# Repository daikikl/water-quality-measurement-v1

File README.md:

# Water-Quality Sensor Test PCB — Research Prototype (2024)

## Purpose

This PCB was designed as a hardware test platform for integrating and evaluating low-cost water-quality sensors within a 2024 university research project.

The broader research proposed a low-cost data-capture strategy for monitoring a tributary of the Paraná River in Encarnación, Paraguay.

## Validation status

The PCB was designed and used as part of the sensor-testing stage of the research project.

Specific test results, sensor calibration procedures, measurement datasets, firmware, and broader system-validation details are described only to the extent authorized by the project team and the related publication.

## My contribution

I designed the PCB used as a test platform for the water-quality sensors in this research project.

The board integrates:

- A LilyGO TTGO T3 LoRa32 development board interface.
- RS-485 communication support through a MAX485 transceiver.
- Terminal connections for multiple water-quality sensors.
- Power connections and auxiliary interfaces for prototype testing.

My contribution was focused on PCB design and hardware integration for sensor testing. I did not claim authorship of the complete monitoring strategy, firmware, data analysis, or all experimental validation activities.

## Related publication

Liebel, D., Lugo, D., & Kawamura, D. (2024). *Estrategia de captura de datos con sensores de bajo costo para la gestión de calidad de agua del afluente del Río Paraná*. Revista Impacto, 4(1), 1–12.

[Read the publication](https://revistas.uni.edu.py/index.php/impacto/article/view/504)

## PCB layout

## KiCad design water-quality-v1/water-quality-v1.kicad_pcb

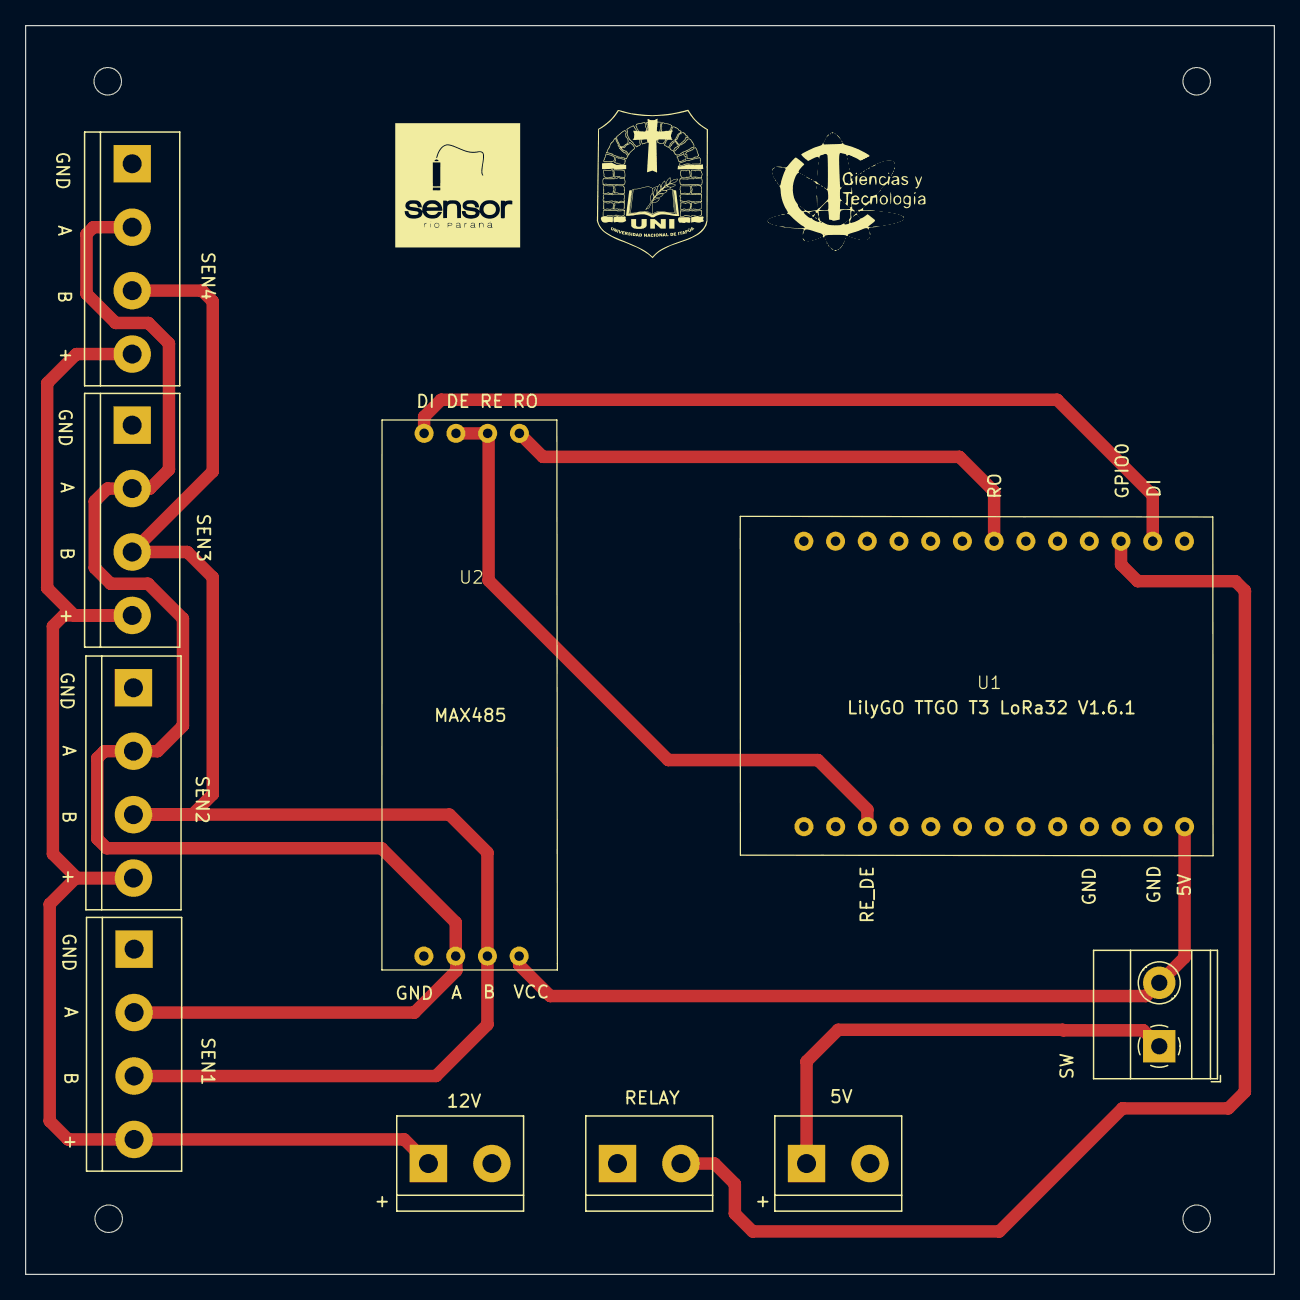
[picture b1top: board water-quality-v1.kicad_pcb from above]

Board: 2 copper layers, 100.0 x 100.0 mm, 14 parts (0 on the bottom side), 10 nets.

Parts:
H1, H2, H3, H4: MountingHole; MountingHole_2.2mm_M2
J1, J6, J7: Conn_01x02; TerminalBlock_bornier-2_P5.08mm
J2, J3, J4, J8: Conn_01x04; TerminalBlock_bornier-4_P5.08mm
SW1: SW_DPST_x2; TerminalBlock_Phoenix_MKDS-1,5-2-5.08_1x02_P5.08mm_Horizont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
U1: LilyGO TTGO T3 LoRa32 433MHz V1.6.1 ESP32; LILYGO®TTGO_LoRa32_V2.1
U2: MAX485E; MAX485 HW-097

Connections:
+5V: J1.1, SW1.1 (A)
+12V: J2.4, J3.4, J4.4, J7.1, J8.4
/DI: U1.4 (IO4), U2.4 (DI)
/RELAY: J6.2, U1.0 (IO0)
/RE_DE: U1.3 (RXD), U2.2 (~RE), U2.3 (DE)
/RO: U1.12 (IO12), U2.1 (RO)
/Vcc: SW1.2 (B), U1.5V, U2.8 (VCC)
GND: J1.2, J2.1, J3.1, J4.1, J7.2, J8.1, U1.GND, U2.5 (GND)
unnamed: J2.2, J3.2, J4.2, J8.2, U2.6 (A)
unnamed: J2.3, J3.3, J4.3, J8.3, U2.7 (B)
